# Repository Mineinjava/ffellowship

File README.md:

# ffellowship
Frequency Fellowship: Examining Radio Wave Propagation from a High Altitude Balloon
---

This is a project for Hack Club's [Apex](https://apex.hackclub.com),
made by:
- [Marcus Kauffman](https://kauffman.tools) KN6UYL (@mineinjava)
- Hudson Hilal (@hhilal123)
- Joshua Truman (@jstruman4929)

We initially had two project ideas for Apex: this and dropping what was
effectively a lawn dart from 100,000 feet. After the lawn dart project
was rejected, we submitted this project.

Many high altitude balloons (HABs) have been launched, almost all of
which have some sort of tracker that transmits the balloon's location.
These transmissions are received by stations on the ground and then
uploaded to the internet, from which we can view the locations of
receiving stations for analysis. Our goal for this project is to study
the differences between different tracker design techniques,
specifically:

- Does radio band selection influence likelihood of reception?
    - Receiving stations on the 2m band are much more common than those
      on the 20m band, but 20m transmissions theoretically travel
      farther.
- There are three common methods of modulating signals:
    - Connecting to a dedicated radio for transmission
    - Using a MS5351M or similar clock generator IC
    - Using [fancy PLL](https://github.com/kaduhi/pico-fractional-pll)
      to "bit-bang" the radio waveform

    **Question: do these three modulation methods have a significant
    difference in quality and therefore propagation?**
- How do different antenna designs affect propagation.

Due to customs issues, we were only able to test the PLL tracker 
with three antenna wavelengths. Two of the frequencies had issues 
(unresolved ATM), so we instead analyzed the effect of height on 
radio wave propagation.

As suggested above, this project can easily be divided into three
"sub-projects":

## 1. Use of the MS5351M Clock Generator IC.

This subproject revolves around the MS5351M clock generator. It features
a custom PCB. Note that this tracker will transmit on both the 20m and
2m bands because the MS5351M has multiple clock generators.

This tracker has quite a few features, many of which are to support
ultra-low power operation, as is common with this style of tracker:

- GPS
- Temperature/pressure sensor
- Shunt
- 3v3 buck-boost converter
- power supervisor to restart the pico
- Sensors can be powered off to conserve power.

This PCB is designed around the Raspberry Pi Pico due to its rigorous
testing and ease of integration. It also features mainly 1206 components
to aid in manual reflow soldering of the PCB.

See the dPicoTracker/ directory for more info.

## 2. Use of PLL:

This subproject uses the Raspberry Pi Pico to generate RF signals,
*without the use of a dedicated radio/chip*. It is by far the simplest
design and features a power supervisor, optional low-pass filter, 
battery measurement circuitry, as well as a GPS which is essential 
for correcting oscillator drift.

## 3. Use of a Dedicated HT Radio.

This subproject uses a Raspberry Pi Zero W and a custom PCB to connect
to a HT, which will be stripped down to save weight. 

The PCB consists of a voltage regulator to power the Pi and a 555 timer
circuit to ensure that transmissions are limited in time (in case
of a software crash).

## Integration:

*coming soon*

## Project Status:

*coming soon*

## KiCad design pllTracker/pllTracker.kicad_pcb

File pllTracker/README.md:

# Tracker using PLL

This tracker uses fractional PLL to generate RF on the 20m band.

## BOM:

| Id  | Designator     | Footprint                         | Quantity | Designation         | Supplier and ref |
|-----|----------------|-----------------------------------|----------|---------------------|------------------|
| 1   | C15            | C_1206_3216Metric                 | 1        | 300pF               |   C5449026       |
| 2   | C14,C16        | C_1206_3216Metric                 | 2        | 180pF               |   C3832761       |
| 3   | R6             | C_1206_3216Metric                 | 1        | 100kΩ               |   C137393        |
| 4   | U7             | SOT-23_ONS                        | 1        | MAX809STRG          |   C9965          |
| 6   | R1             | C_1206_3216Metric                 | 1        | 10kΩ                |   C132649        |
| 7   | L5,L4          | L_1206_3216Metric                 | 2        | 560nH               |   C13585         |
| 10  | IC1            | ATGM336H5N31                      | 1        | ATGM336H-5N31       |   C2940946       |
| 11  | C8             | C_1206_3216Metric                 | 2        | 100nF               |   C137393        |
| 13  | Q1, Q2         | Q_SOT-23                          | 1        | AO3401A             |   C15127         |
| 13  | C7             | C_1206_3216Metric                 | 1        | 1nF                 |   C23631         |
| 14  | R5             | D_1206_3216Metric                 | 1        | 200kΩ               |   C114937        |

Additionally:
- 1 GPS antenna
- 1 20m antenna
- 1 Raspberry Pi Pico

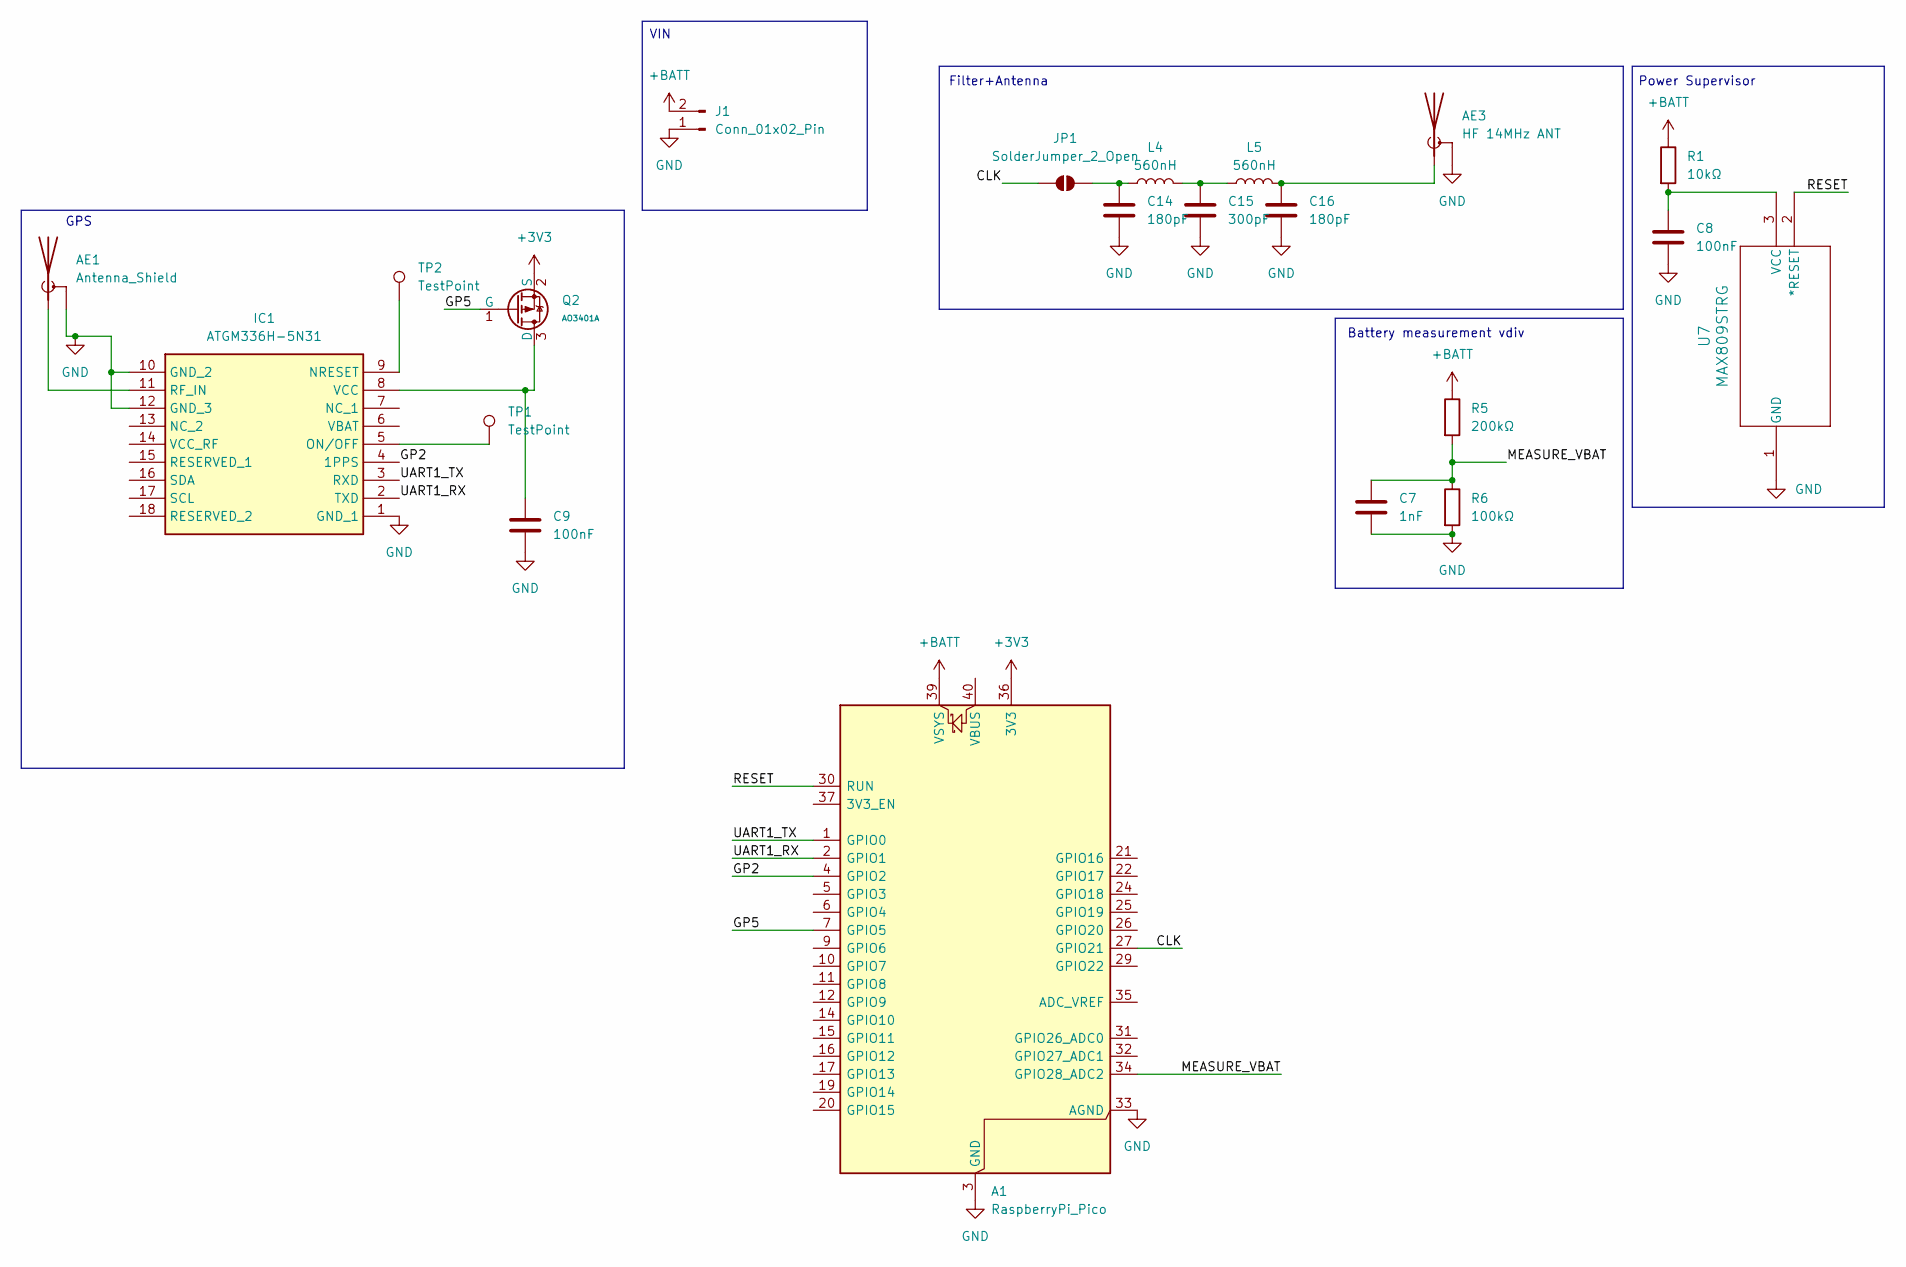
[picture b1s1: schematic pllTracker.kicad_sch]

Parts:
A1: RaspberryPi_Pico; RaspberryPi_Pico_Common_Unspecified
AE1: Antenna_Shield; PinSocket_1x02_P2.54mm_Vertical
AE3: HF 14MHz ANT; PinHeader_1x02_P2.54mm_Vertical
C7: 1nF; C_1206_3216Metric
C8, C9: 100nF; C_1206_3216Metric
C14, C16: 180pF; C_1206_3216Metric
C15: 300pF; C_1206_3216Metric
IC1: ATGM336H-5N31; ATGM336H5N31; Manufacturer_Part_Number ATGM336H-5N31
J1: Conn_01x02_Pin; PinSocket_1x02_P2.54mm_Vertical
JP1: SolderJumper_2_Open; SolderJumper-2_P1.3mm_Open_Pad1.0x1.5mm
L4, L5: 560nH; L_1206_3216Metric
Q2: AO3401A; Q_SOT-23; Part AO3401A; LCSC C15127
R1: 10kΩ; C_1206_3216Metric
R5: 200kΩ; D_1206_3216Metric
R6: 100kΩ; C_1206_3216Metric
TP1, TP2: TestPoint; TestPoint_Pad_D1.5mm
U7: MAX809STRG; SOT-23_ONS

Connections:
+3V3: A1.36 (3V3), Q2.2 (S)
+BATT: A1.39 (VSYS), J1.2, R1.1, R5.1
/CLK: A1.27 (GPIO21), JP1.1 (A)
/GP2: A1.4 (GPIO2), IC1.4 (1PPS)
/GP5: A1.7 (GPIO5), Q2.1 (G)
/MEASURE_VBAT: A1.34 (GPIO28_ADC2), C7.2, R5.2, R6.1
/RESET: A1.30 (RUN), U7.2 (*RESET)
/UART1_RX: A1.2 (GPIO1), IC1.2 (TXD)
/UART1_TX: A1.1 (GPIO0), IC1.3 (RXD)
GND: A1.3 (GND), A1.8 (GND), A1.13 (GND), A1.18 (GND), A1.23 (GND), A1.28 (GND), A1.33 (AGND), A1.38 (GND), AE1.2 (Shield), AE3.2 (Shield), C7.1, C8.2, C9.2, C14.2, C15.2, C16.2, IC1.1 (GND_1), IC1.10 (GND_2), IC1.12 (GND_3), J1.1, R6.2, U7.1 (GND)
unnamed: AE1.1 (A), IC1.11 (RF_IN)
unnamed: AE3.1 (A), C16.1, L5.2
unnamed: C15.1, L4.2, L5.1
unnamed 13: IC1.9 (NRESET), TP2.1; also elsewhere on the board
unnamed 14: IC1.5 (ON/OFF), TP1.1; also elsewhere on the board
unnamed: C9.1, IC1.8 (VCC), Q2.3 (D)
unnamed: C14.1, JP1.2 (B), L4.1
unnamed: C8.1, R1.2, U7.3 (VCC)

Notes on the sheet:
Power Supervisor
VIN
GPS
Filter+Antenna
Battery measurement vdiv

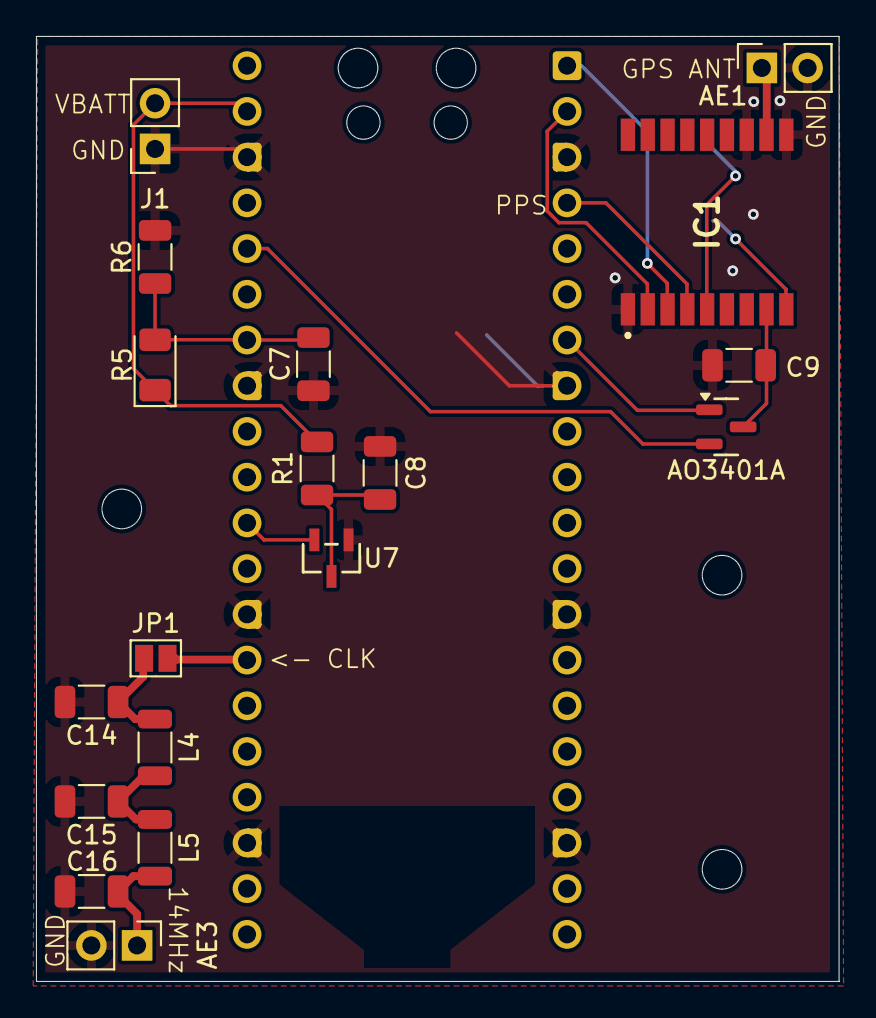
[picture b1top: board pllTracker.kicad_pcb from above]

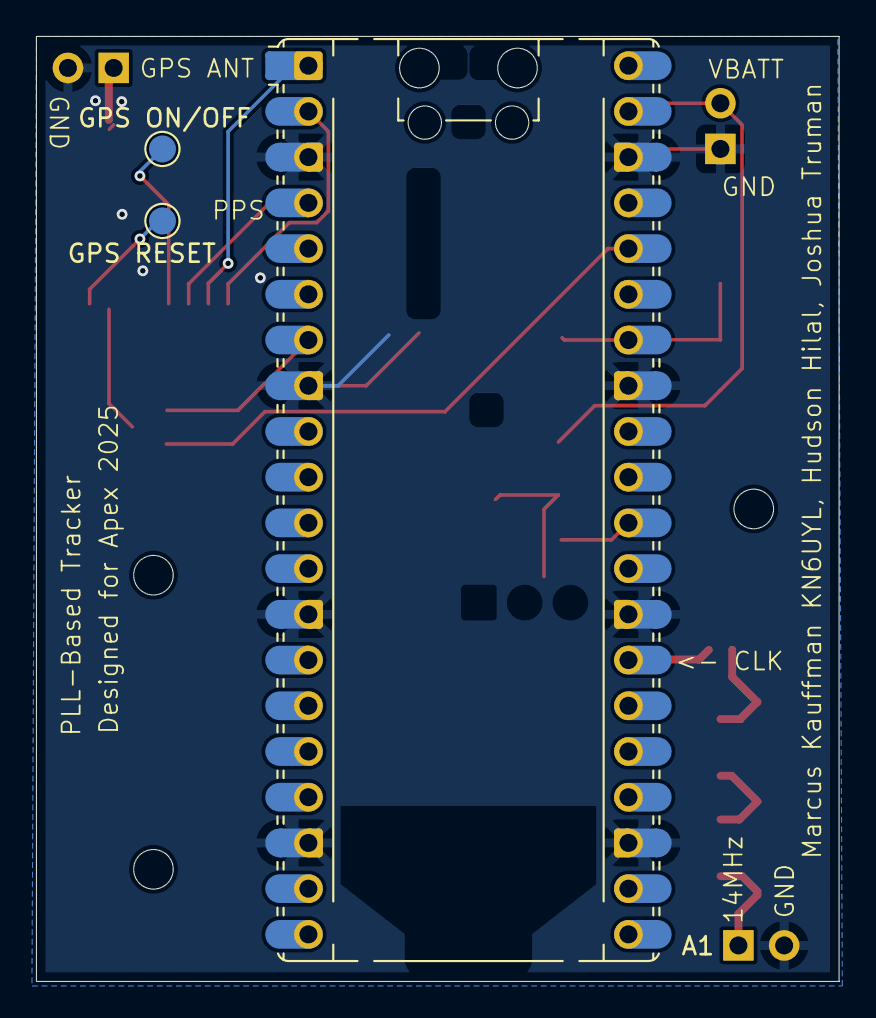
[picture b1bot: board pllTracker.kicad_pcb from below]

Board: 2 copper layers, 44.6 x 52.5 mm, 21 parts (3 on the bottom side), 18 nets.

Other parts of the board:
GPS ON/OFF: TestPoint; TestPoint_Pad_D1.5mm
GPS RESET: TestPoint; TestPoint_Pad_D1.5mm

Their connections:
unnamed 13: GPS RESET.1; also elsewhere on the board
unnamed 14: GPS ON/OFF.1; also elsewhere on the board

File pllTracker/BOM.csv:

Comment,Designator,Footprint,LCSC Part #,Quantity
300pF,C15,C_1206_3216Metric,C5449026,1
180pF,C14C16,C_1206_3216Metric,C3832761,2
100kΩ,R6,C_1206_3216Metric,C137393,1
MAX809STRG,U7,SOT-23_ONS,C9965,1
10kΩ,R1,C_1206_3216Metric,C132649,1
560nH,L5L4,L_1206_3216Metric,C13585,2
ATGM336H-5N31,IC1,ATGM336H5N31,C2940946,1
100nF,C8,C_1206_3216Metric,C137393,2
AO3401A,Q1Q2,Q_SOT-23,C15127,1
1nF,C7,C_1206_3216Metric,C23631,1
200kΩ,R5,D_1206_3216Metric,C114937,1

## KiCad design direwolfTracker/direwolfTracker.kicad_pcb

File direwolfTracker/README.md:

# Direwolf-powered Tracker

This tracker uses direwolf to communicate with an external radio like a
HT.

## BOM:

| Id  | Designator           | Footprint                           | Quantity | Designation       | Supplier and ref |
|-----|----------------------|-------------------------------------|----------|-------------------|------------------|
| 1   | C2, C1, C3           | C_1206_3216Metric                   | 3        | 10µF              |    C13585        |
| 3   | Q1                   | Q_SOT-23                            | 1        | MMBT2222A         |    C82460        |
| 4   | C20, C19, C21        | C_1206_3216Metric                   | 3        | 100nF             |    C82460        |
| 7   | U1                   | Texas_R-PDSO-G6                     | 1        | TPS61222DCK       |    C116461       |
| 9   | R1                   | R_1206_3216Metric                   | 1        | 10kΩ              |    C132649       |
| 10  | R3                   | R_1206_3216Metric                   | 1        | 2.7kΩ             |    C2930416      |
| 12  | IC1                  | ATGM336H5N31                        | 1        | ATGM336H-5N31     |    C2940946      |
| 13  | R2                   | R_1206_3216Metric                   | 1        | 100kΩ             |    C2930416      |
| 14  | U2                   | DIP-8_W7.62mm                       | 1        | ICM7555xP         |    C22461592     |
| 15  | R4                   | R_1206_3216Metric                   | 1        | 1MΩ               |    C108083       |
| 16  | L1                   | L_1206_3216Metric                   | 1        | 4.7µH             |    C13585        |

Additionally:
- 1 Raspberry Pi Zero
- 1 GPS Antenna
- 1 micro usb sound card
- 1 TRRS 3.5mm cable
- 1 TRS 3.5mm cable
- 1 TRS 2.5mm cable
- 1 external radio

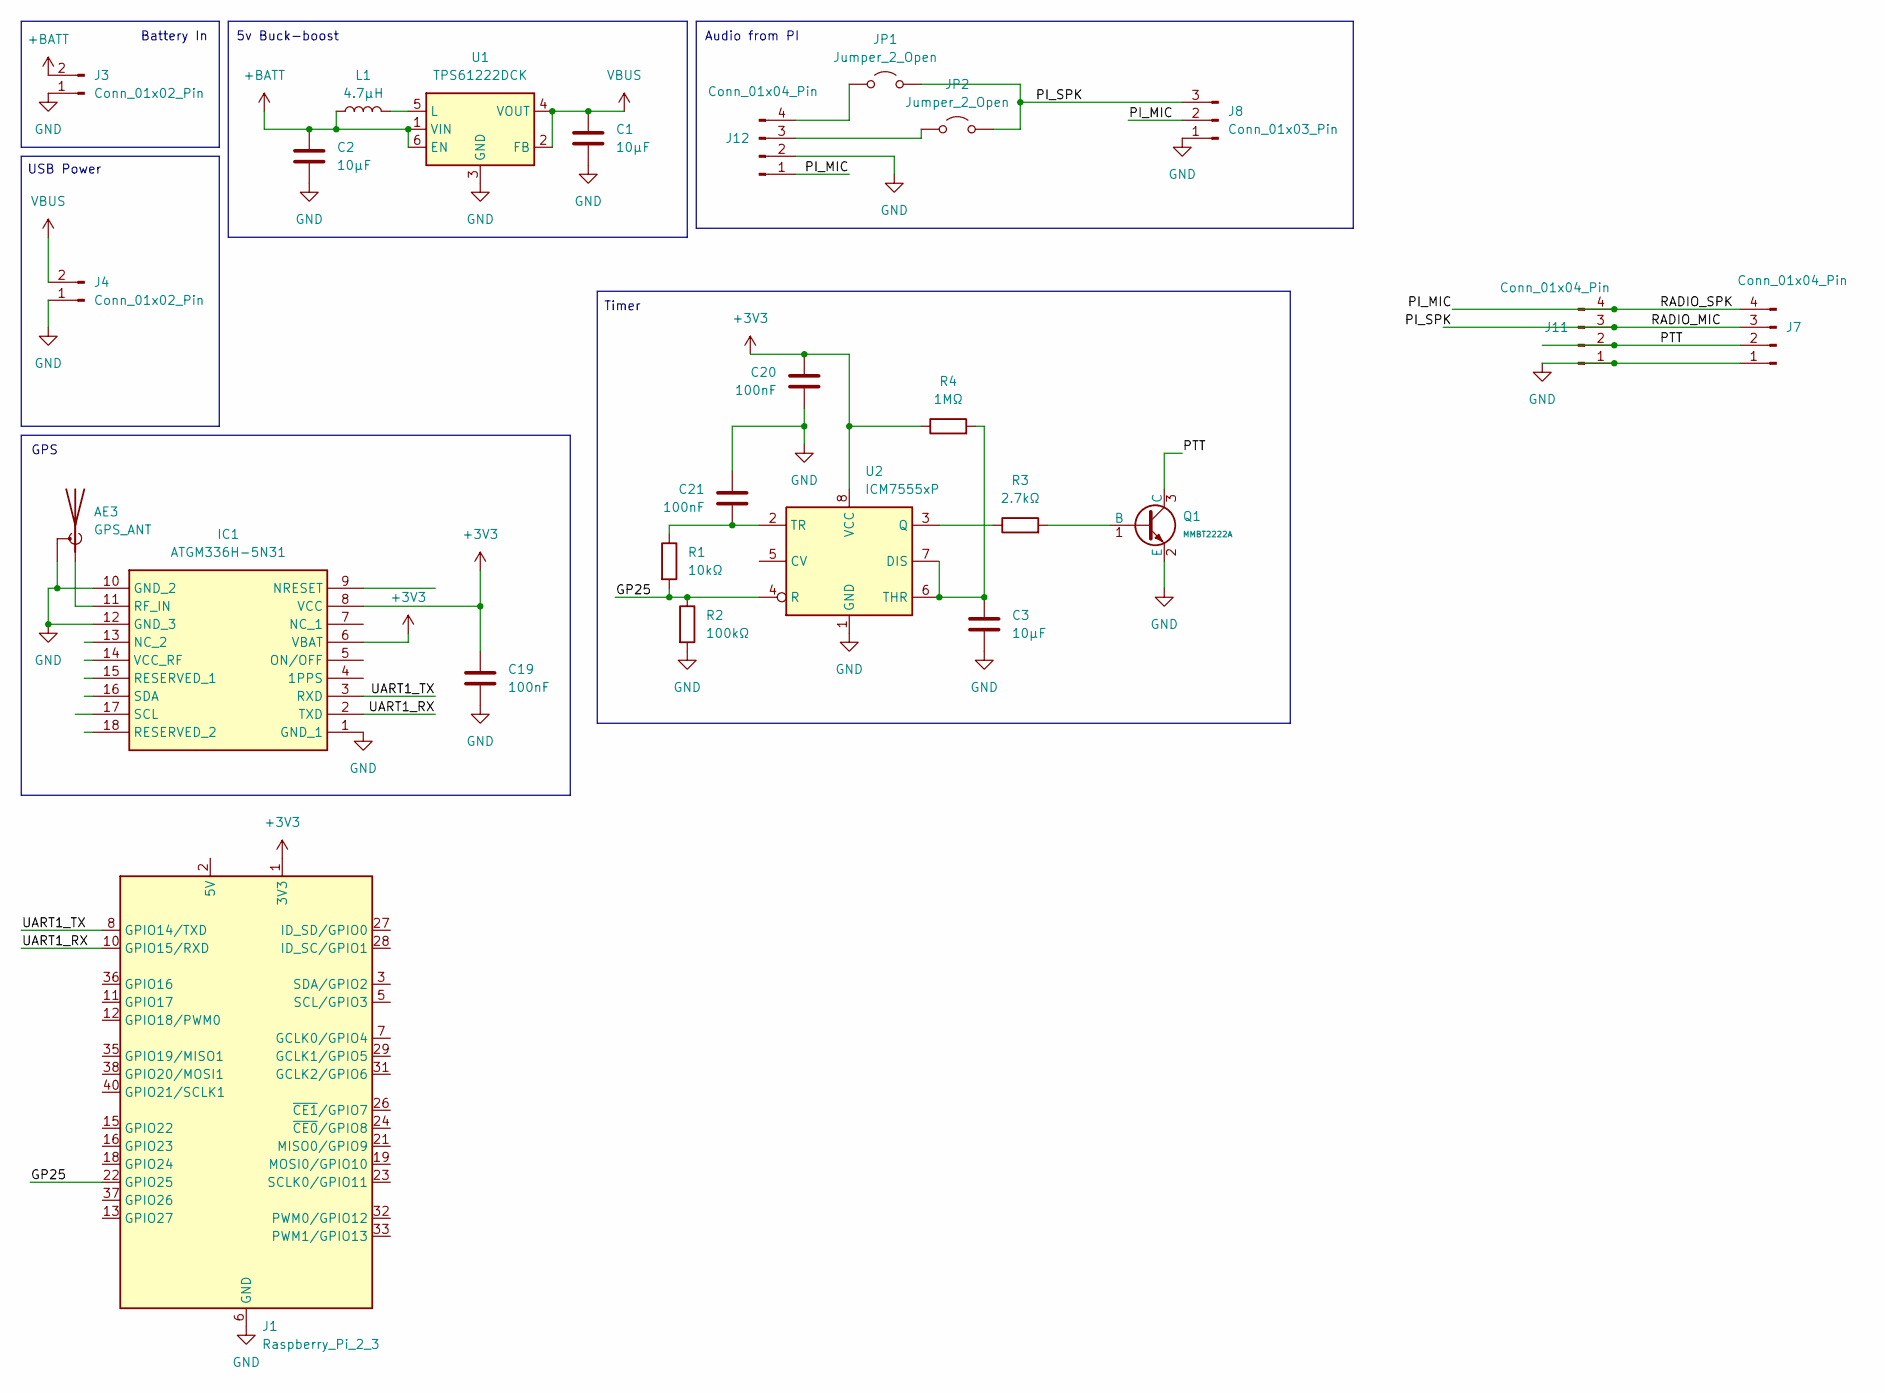
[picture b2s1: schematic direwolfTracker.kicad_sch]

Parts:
AE3: GPS_ANT; PinHeader_1x02_P2.54mm_Vertical
C1, C2, C3: 10µF; C_1206_3216Metric
C19, C20, C21: 100nF; C_1206_3216Metric
IC1: ATGM336H-5N31; ATGM336H5N31; Manufacturer_Part_Number ATGM336H-5N31
J1: Raspberry_Pi_2_3; PinHeader_2x20_P2.54mm_Vertical
J3, J4: Conn_01x02_Pin; PinSocket_1x02_P2.54mm_Vertical
J7, J11, J12: Conn_01x04_Pin; PinHeader_1x04_P2.54mm_Vertical
J8: Conn_01x03_Pin; PinSocket_1x03_P2.54mm_Vertical
JP1, JP2: Jumper_2_Open; TestPoint_2Pads_Pitch2.54mm_Drill0.8mm
L1: 4.7µH; L_1206_3216Metric
Q1: MMBT2222A; Q_SOT-23; Part MMBT2222A; LCSC C7420351
R1: 10kΩ; R_1206_3216Metric
R2: 100kΩ; R_1206_3216Metric
R3: 2.7kΩ; R_1206_3216Metric
R4: 1MΩ; R_1206_3216Metric
U1: TPS61222DCK; Texas_R-PDSO-G6
U2: ICM7555xP; DIP-8_W7.62mm

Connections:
+3V3: C19.1, C20.1, IC1.6 (VBAT), IC1.8 (VCC), J1.1 (3V3), J1.17 (3V3), R4.1, U2.8 (VCC)
+BATT: C2.1, J3.2, L1.1, U1.1 (VIN), U1.6 (EN)
/GP25: J1.22 (GPIO25), R1.2, R2.1, U2.4 (R)
/PI_MIC: J7.4, J8.2, J11.4, J12.1
/PI_SPK: J7.3, J8.3, J11.3, JP1.2 (B), JP2.2 (B)
/PTT: J7.2, J11.2, Q1.3 (C)
/UART1_RX: IC1.2 (TXD), J1.10 (GPIO15/RXD)
/UART1_TX: IC1.3 (RXD), J1.8 (GPIO14/TXD)
GND: AE3.2 (Shield), C1.2, C2.2, C3.2, C19.2, C20.2, C21.1, IC1.1 (GND_1), IC1.10 (GND_2), IC1.12 (GND_3), J1.6 (GND), J1.9 (GND), J1.14 (GND), J1.20 (GND), J1.25 (GND), J1.30 (GND), J1.34 (GND), J1.39 (GND), J3.1, J4.1, J7.1, J8.1, J11.1, J12.2, Q1.2 (E), R2.2, U1.3 (GND), U2.1 (GND)
unnamed: AE3.1 (A), IC1.11 (RF_IN)
unnamed: J1.2 (5V), J1.4 (5V)
unnamed: J12.3, JP2.1 (A)
unnamed: J12.4, JP1.1 (A)
unnamed: Q1.1 (B), R3.2
unnamed: L1.2, U1.5 (L)
unnamed: C3.1, R4.2, U2.6 (THR), U2.7 (DIS)
unnamed: R3.1, U2.3 (Q)
unnamed: C21.2, R1.1, U2.2 (TR)
VBUS: C1.1, J4.2, U1.2 (FB), U1.4 (VOUT)

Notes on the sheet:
Battery In
GPS
5v Buck-boost
Timer
Audio from PI
USB Power

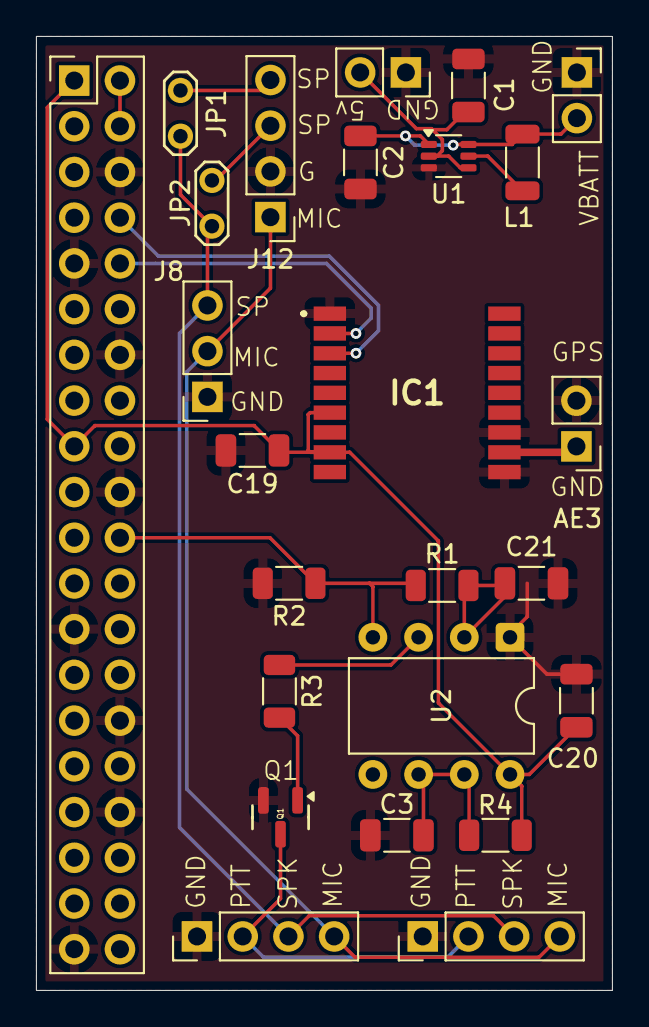
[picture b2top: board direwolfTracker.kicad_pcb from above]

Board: 2 copper layers, 32.0 x 53.0 mm, 25 parts (0 on the bottom side), 19 nets.

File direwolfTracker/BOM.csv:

Comment,Designator,Footprint,LCSC Part #,Quantity
10µF,C2C1C3,C_1206_3216Metric,C13585,3
MMBT2222A,Q1,Q_SOT-23,C82460,1
100nF,C20C19C21,C_1206_3216Metric,C82460,3
TPS61222DCK,U1,Texas_R-PDSO-G6,C116461,1
10kΩ,R1,R_1206_3216Metric,C132649,1
2.7kΩ,R3,R_1206_3216Metric,C2930416,1
ATGM336H-5N31,IC1,ATGM336H5N31,C2940946,1
100kΩ,R2,R_1206_3216Metric,C2930416,1
ICM7555xP,U2,DIP-8_W7.62mm,C22461592,1
1MΩ,R4,R_1206_3216Metric,C108083,1
4.7µH,L1,L_1206_3216Metric,C13585,1

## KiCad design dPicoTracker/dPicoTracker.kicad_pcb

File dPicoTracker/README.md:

# Tracker With MS5351M IC

This tracker uses the MS5351M IC to generate RF.

## BOM:

| Id  | Designator                        | Footprint                                         | Quantity | Designation         | Supplier and ref | 
|-----|----------------------------------|---------------------------------------------------|----------|----------------------|------------------|
| 1   | L1                               | L_1206_3216Metric                                 | 1        | 4.7µH               |      C13585       |
| 2   | C14, C16                         | C_1206_3216Metric                                 | 2        | 18pF                |      C565686      |
| 3   | L4, L5                           | L_1206_3216Metric                                 | 2        | 56nH                |      C13585       |
| 4   | U7                               | SOT-23_ONS                                        | 1        | MAX809STRG          |      C9965        |
| 6   | U8                               | Bosch_LGA-8_2x2.5mm_P0.65mm                       | 1        | BMP280              |      C83291       |
| 7   | Y1                               | MSOP-10_3x3mm_P0.5mm                              | 1        | Si5351A-B-GT        |      C1509083     |
| 8   | C9, C19, C1, C8, C17, C18, C10   | C_1206_3216Metric                                 | 7        | 100nF               |      C24497       |
| 10  | Y2                               | Crystal_SMD_2520-4Pin_2.5x2.0mm                   | 1        | C132296             |      C132296      |
| 11  | L3, L2                           | L_1206_3216Metric                                 | 2        | 560nH               |      C13585       |
| 12  | R6                               | C_1206_3216Metric                                 | 1        | 100kΩ               |      C137393      |
| 13  | Q1, Q2                           | Q_SOT-23                                          | 2        | AO3401A             |      C15127       |
| 15  | R8, R14, R15, R11, R9, R12       | R_1206_3216Metric                                 | 6        | 10kΩ                |      C132649      |
| 16  | C15                              | C_1206_3216Metric                                 | 1        | 30pF                |      C1905        |
| 17  | C12                              | C_1206_3216Metric                                 | 1        | 300pF               |      C5449026     |
| 18  | C5                               | C_1206_3216Metric                                 | 1        | 10µF                |      C13585       |
| 19  | C11, C13                         | C_1206_3216Metric                                 | 2        | 180pF               |      C3832761     |
| 20  | IC1                              | ATGM336H5N31                                      | 1        | ATGM336H-5N31       |      C2940946     |
| 21  | U3, U4                           | SOT-23-3_L2.9-W1.6-P1.90-LS2.8-BR                 | 2        | CJ431               |      C3113        |
| 22  | R7                               | C_1206_3216Metric                                 | 1        | 10kΩ                |      C132649      |
| 23  | U5                               | Texas_R-PDSO-G6                                   | 1        | TPS61221DCK         |      C2865756     |
| 24  | C7                               | C_1206_3216Metric                                 | 1        | 1nF                 |      C23631       |
| 25  | R5                               | D_1206_3216Metric                                 | 1        | 200kΩ               |      C114937      |

Additionally:
- 1x GPS antenna
- 1x 2m antenna
- 1x 20m antenna
- 1x Raspberry Pi Pico

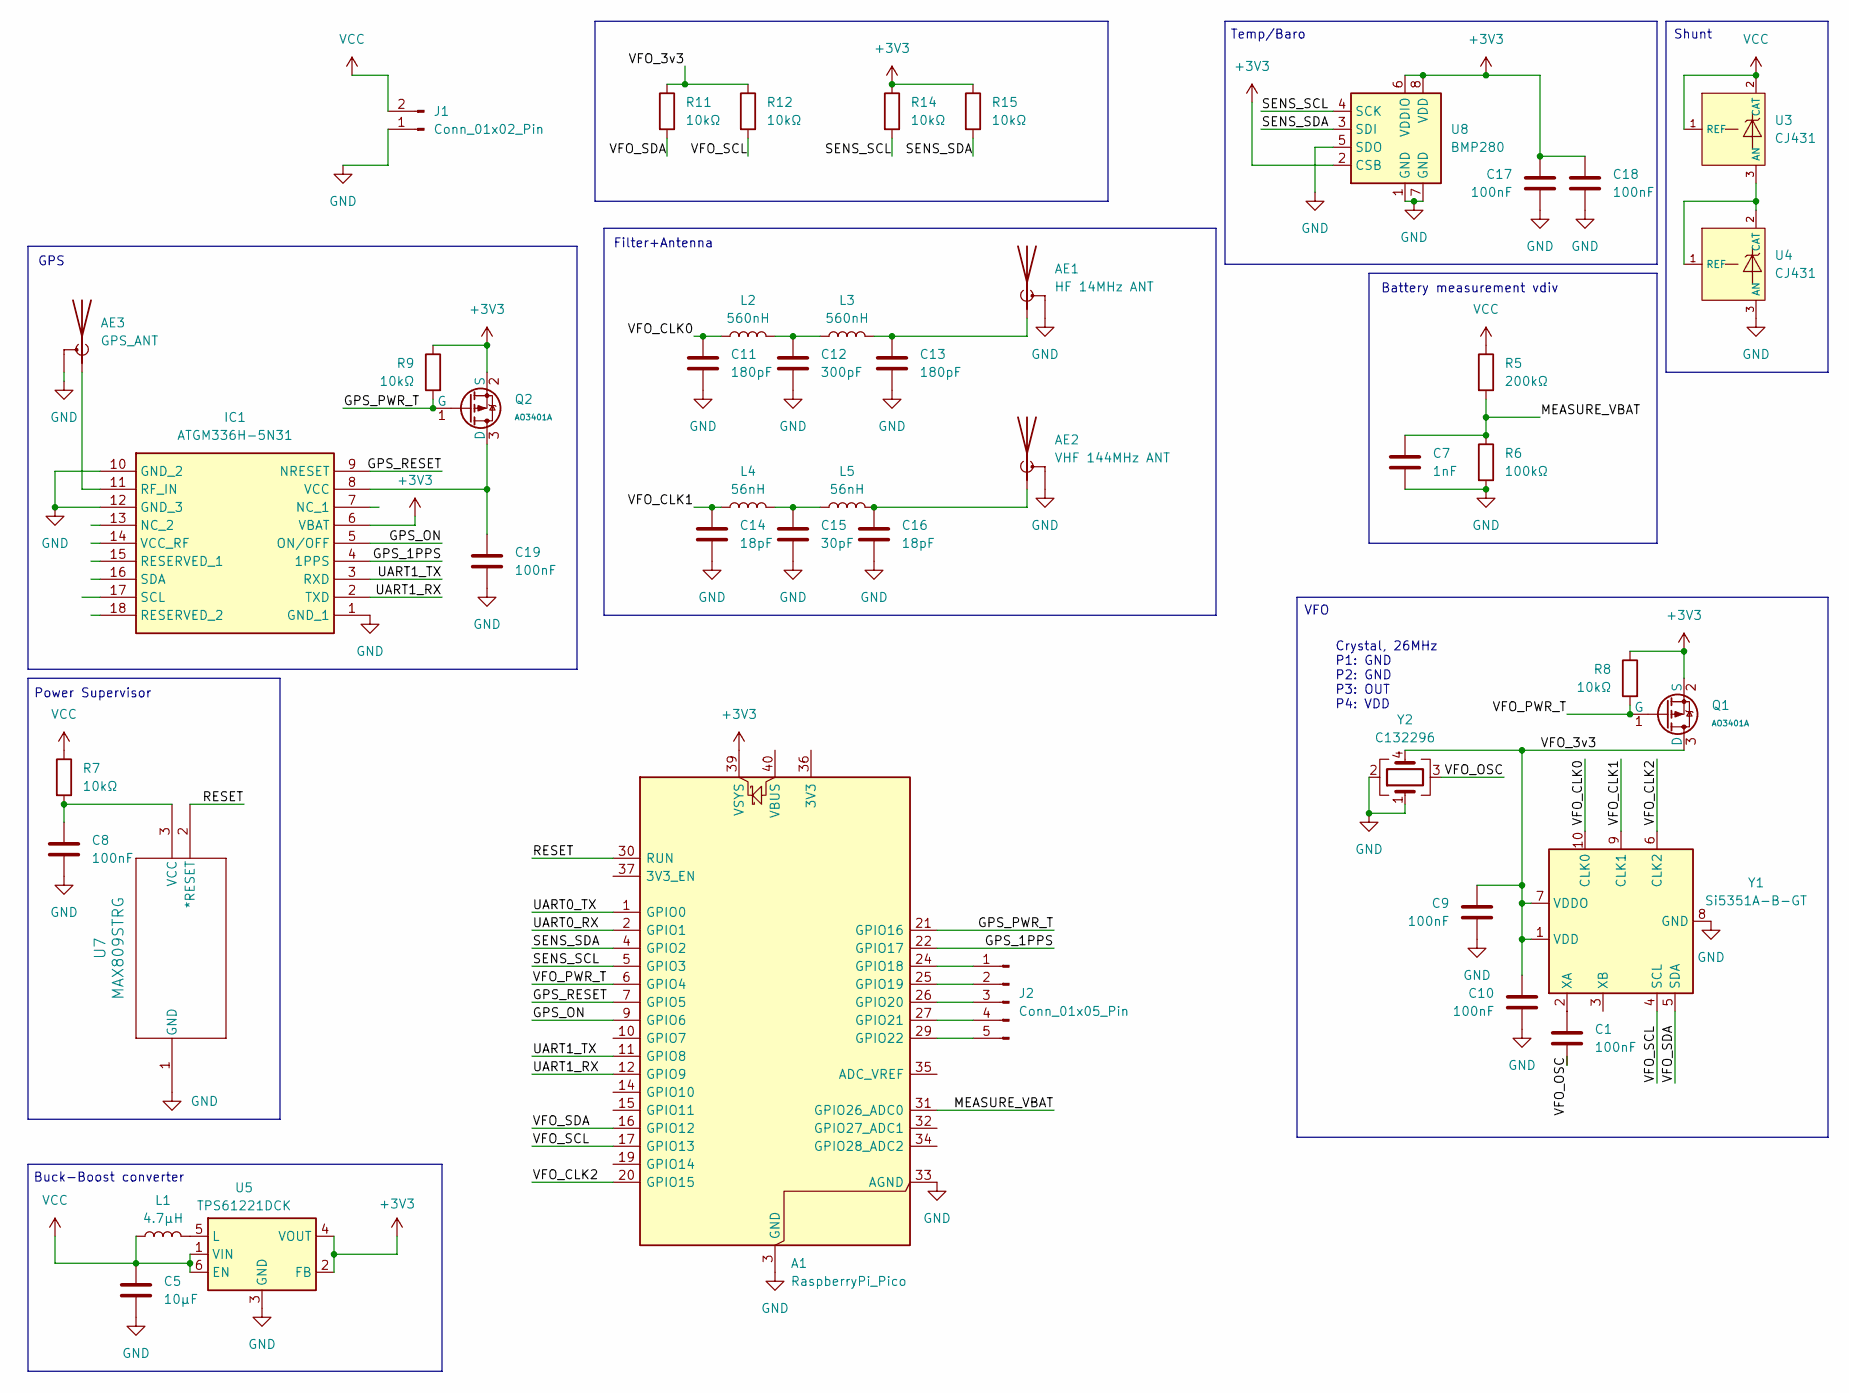
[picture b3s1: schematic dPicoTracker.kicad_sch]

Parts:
A1: RaspberryPi_Pico; RaspberryPi_Pico_Common_Unspecified
AE1: HF 14MHz ANT; PinHeader_1x02_P2.54mm_Vertical
AE2: VHF 144MHz ANT; PinHeader_1x02_P2.54mm_Vertical
AE3: GPS_ANT; PinHeader_1x02_P2.54mm_Vertical
C1, C8, C9, C10, C17, C18, C19: 100nF; C_1206_3216Metric
C5: 10µF; C_1206_3216Metric
C7: 1nF; C_1206_3216Metric
C11, C13: 180pF; C_1206_3216Metric
C12: 300pF; C_1206_3216Metric
C14, C16: 18pF; C_1206_3216Metric
C15: 30pF; C_1206_3216Metric
IC1: ATGM336H-5N31; ATGM336H5N31; Manufacturer_Part_Number ATGM336H-5N31
J1: Conn_01x02_Pin; PinSocket_1x02_P2.00mm_Vertical
J2: Conn_01x05_Pin; PinSocket_1x05_P2.54mm_Vertical
L1: 4.7µH; L_1206_3216Metric
L2, L3: 560nH; L_1206_3216Metric
L4, L5: 56nH; L_1206_3216Metric
Q1, Q2: AO3401A; Q_SOT-23; Part AO3401A; LCSC C15127
R5: 200kΩ; D_1206_3216Metric
R6: 100kΩ; C_1206_3216Metric
R7: 10kΩ; C_1206_3216Metric
R8, R9, R11, R12, R14, R15: 10kΩ; R_1206_3216Metric
U3, U4: CJ431; SOT-23-3_L2.9-W1.6-P1.90-LS2.8-BR; Output Voltage 2.5V~36V; Tolerance ±0.5%; Part CJ431; LCSC C3113
U5: TPS61221DCK; Texas_R-PDSO-G6
U7: MAX809STRG; SOT-23_ONS
U8: BMP280; Bosch_LGA-8_2x2.5mm_P0.65mm_ClockwisePinNumbering
Y1: Si5351A-B-GT; MSOP-10_3x3mm_P0.5mm
Y2: C132296; Crystal_SMD_2520-4Pin_2.5x2.0mm

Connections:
+3V3: A1.39 (VSYS), C17.1, C18.1, IC1.6 (VBAT), Q1.2 (S), Q2.2 (S), R8.1, R9.1, R14.1, R15.1, U5.2 (FB), U5.4 (VOUT), U8.2 (CSB), U8.6 (VDDIO), U8.8 (VDD)
/GPS_1PPS: A1.22 (GPIO17), IC1.4 (1PPS)
/GPS_ON: A1.9 (GPIO6), IC1.5 (ON/OFF)
/GPS_PWR_T: A1.21 (GPIO16), Q2.1 (G), R9.2
/GPS_RESET: A1.7 (GPIO5), IC1.9 (NRESET)
/MEASURE_VBAT: A1.31 (GPIO26_ADC0), C7.2, R5.2, R6.1
/RESET: A1.30 (RUN), U7.2 (*RESET)
/SENS_SCL: A1.5 (GPIO3), R14.2, U8.4 (SCK)
/SENS_SDA: A1.4 (GPIO2), R15.2, U8.3 (SDI)
/UART0_RX: A1.2 (GPIO1)
/UART0_TX: A1.1 (GPIO0)
/UART1_RX: A1.12 (GPIO9), IC1.2 (TXD)
/UART1_TX: A1.11 (GPIO8), IC1.3 (RXD)
/VFO_3v3: C9.1, C10.1, Q1.3 (D), R11.1, R12.1, Y1.1 (VDD), Y1.7 (VDDO), Y2.4
/VFO_CLK0: C11.1, L2.1, Y1.10 (CLK0)
/VFO_CLK1: C14.1, L4.1, Y1.9 (CLK1)
/VFO_CLK2: A1.20 (GPIO15), Y1.6 (CLK2)
/VFO_OSC: C1.1, Y2.3
/VFO_PWR_T: A1.6 (GPIO4), Q1.1 (G), R8.2
/VFO_SCL: A1.17 (GPIO13), R12.2, Y1.4 (SCL)
/VFO_SDA: A1.16 (GPIO12), R11.2, Y1.5 (SDA)
GND: A1.3 (GND), A1.8 (GND), A1.13 (GND), A1.18 (GND), A1.23 (GND), A1.28 (GND), A1.33 (AGND), A1.38 (GND), AE1.2 (Shield), AE2.2 (Shield), AE3.2 (Shield), C5.2, C7.1, C8.2, C9.2, C10.2, C11.2, C12.2, C13.2, C14.2, C15.2, C16.2, C17.2, C18.2, C19.2, IC1.1 (GND_1), IC1.10 (GND_2), IC1.12 (GND_3), J1.1, R6.2, U4.3 (AN), U5.3 (GND), U7.1 (GND), U8.1 (GND), U8.5 (SDO), U8.7 (GND), Y1.8 (GND), Y2.1, Y2.2
unnamed: A1.24 (GPIO18), J2.1
unnamed: A1.25 (GPIO19), J2.2
unnamed: A1.26 (GPIO20), J2.3
unnamed: A1.27 (GPIO21), J2.4
unnamed: A1.29 (GPIO22), J2.5
unnamed: AE1.1 (A), C13.1, L3.2
unnamed: AE2.1 (A), C16.1, L5.2
unnamed: AE3.1 (A), IC1.11 (RF_IN)
unnamed: C12.1, L2.2, L3.1
unnamed: C15.1, L4.2, L5.1
unnamed: C19.1, IC1.8 (VCC), Q2.3 (D)
unnamed: U3.3 (AN), U4.1 (REF), U4.2 (CAT)
unnamed: L1.2, U5.5 (L)
unnamed: C8.1, R7.2, U7.3 (VCC)
unnamed: C1.2, Y1.2 (XA)
VCC: C5.1, J1.2, L1.1, R5.1, R7.1, U3.1 (REF), U3.2 (CAT), U5.1 (VIN), U5.6 (EN)

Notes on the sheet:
Filter+Antenna
Buck-Boost converter
Battery measurement vdiv
GPS
Shunt
Crystal, 26MHz P1: GND P2: GND P3: OUT P4: VDD
Power Supervisor
VFO
Temp/Baro

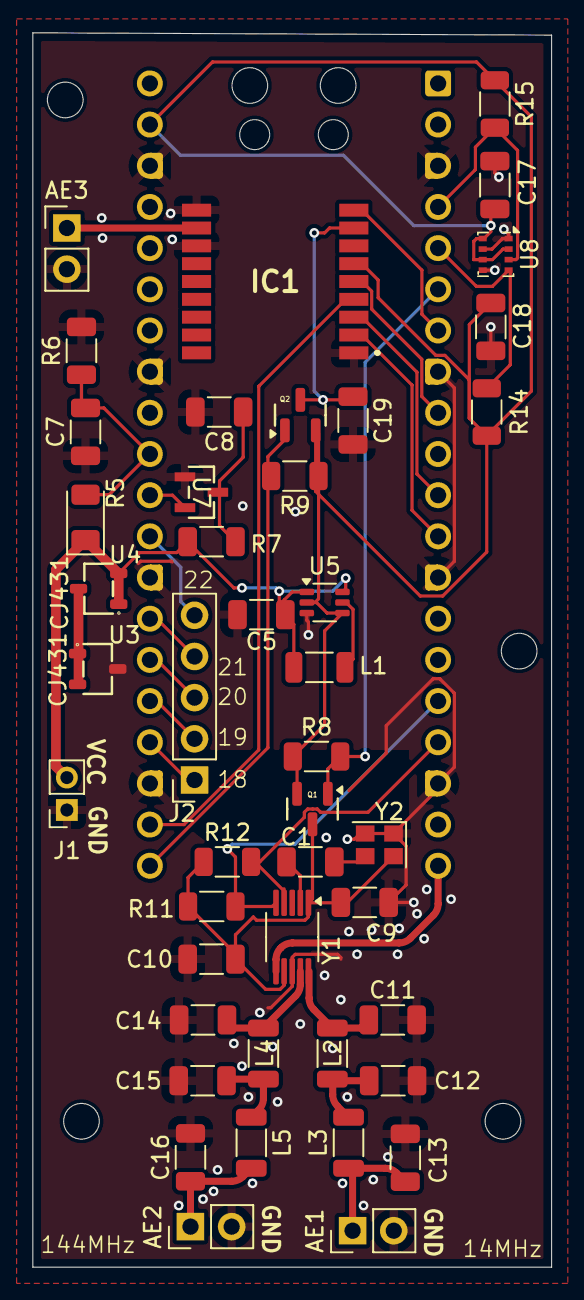
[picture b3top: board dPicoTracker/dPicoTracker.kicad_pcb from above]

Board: 2 copper layers, 32.0 x 76.1 mm, 45 parts (1 on the bottom side), 36 nets.

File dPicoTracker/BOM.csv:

Comment,Designator,Footprint,LCSC Part #,Quantity
4.7µH,L1,L_1206_3216Metric,C13585,1
18pF,C14C16,C_1206_3216Metric,C565686,2
56nH,L4L5,L_1206_3216Metric,C13585,2
MAX809STRG,U7,SOT-23_ONS,C9965,1
BMP280,U8,Bosch_LGA-8_2x2.5mm_P0.65mm,C83291,1
Si5351A-B-GT,Y1,MSOP-10_3x3mm_P0.5mm,C1509083,1
100nF,C9C19C1C8C17C18C10,C_1206_3216Metric,C24497,7
C132296,Y2,Crystal_SMD_2520-4Pin_2.5x2.0mm,C132296,1
560nH,L3L2,L_1206_3216Metric,C13585,2
100kΩ,R6,C_1206_3216Metric,C137393,1
AO3401A,Q1Q2,Q_SOT-23,C15127,2
10kΩ,R8R14R1R11R9R12,R_1206_3216Metric,C132649,6
30pF,C15,C_1206_3216Metric,C1905,1
300pF,C12,C_1206_3216Metric,C5449026,1
10µF,C5,C_1206_3216Metric,C13585,1
180pF,C11C13,C_1206_3216Metric,C3832761,2
ATGM336H-5N31,IC1,ATGM336H5N31,C2940946,1
CJ431,U3U4,SOT-23-3_L2.9-W1.6-P1.90-LS2.8-BR,C3113,2
10kΩ,R7,C_1206_3216Metric,C132649,1
TPS61221DCK,U5,Texas_R-PDSO-G6,C2865756,1
1nF,C7,C_1206_3216Metric,C23631,1
200kΩ,R5,D_1206_3216Metric,C114937,1

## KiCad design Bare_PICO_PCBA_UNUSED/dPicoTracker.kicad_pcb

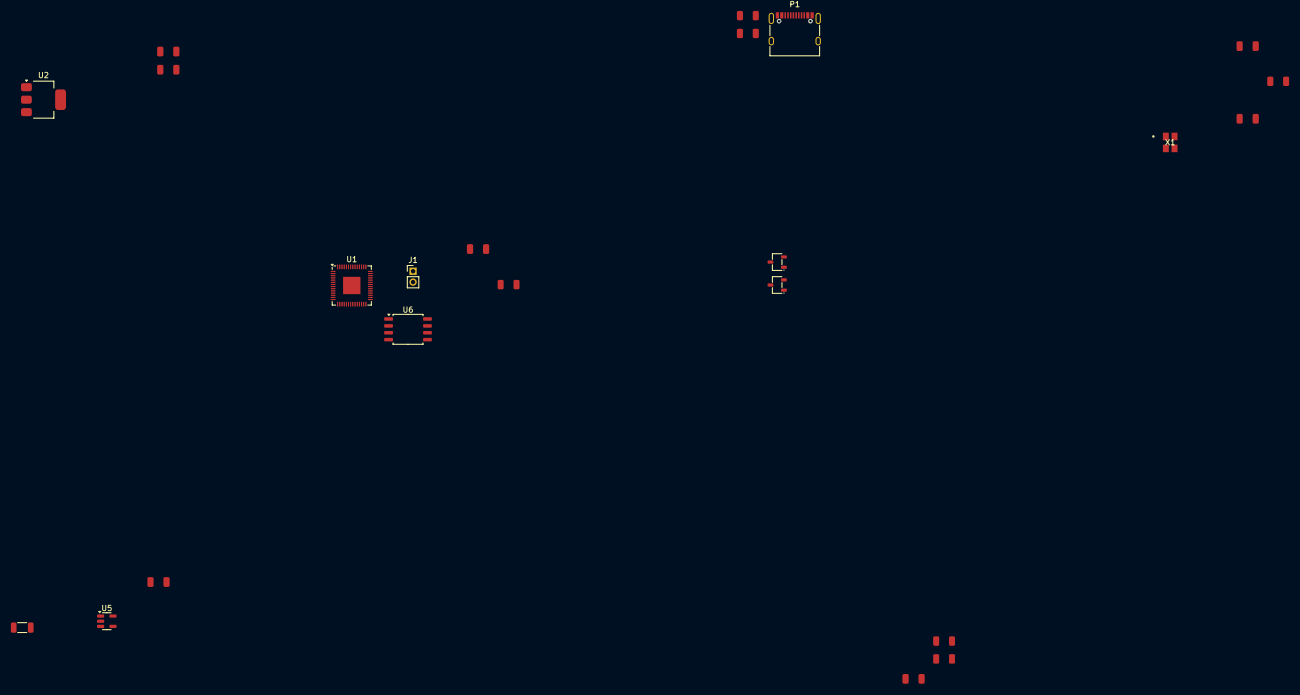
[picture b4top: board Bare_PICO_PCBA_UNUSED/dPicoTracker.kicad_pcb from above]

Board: 2 copper layers, 23 parts (0 on the bottom side), 14 nets, no tracks yet.

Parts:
C1: 100nF; C_1206
C2, C6: 15pF; C_1206
C3, C4, C5: 10µF; C_1206
C7: 1nF; C_1206
J1: Conn_01x02_Pin; PinHeader_1x02_P2.00mm_Vertical
L1: 4.7µH; L_1206
P1: USB_C_Plug_USB2.0; USB_C_Receptacle_XKB_U262-16XN-4BVC11
R1, R2: 5.1kΩ; R_1206
R3, R4: 1kΩ; R_1206
R5: 200kΩ; R_1206
R6: 100kΩ; R_1206
U1: RP2040; QFN-56-1EP_7x7mm_P0.4mm_EP3.2x3.2mm
U2: NCP1117-3.3_SOT223; SOT-223-3_TabPin2
U3, U4: CJ431; SOT-23-3_L2.9-W1.6-P1.90-LS2.8-BR
U5: TPS61221DCK; SOT-23-5
U6: W25Q128JVS; SOIC-8_5.3x5.3mm_P1.27mm
X1: ABM8-272-T3; ABM8-272-T3_ABR

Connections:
+3V3: C1.1, C4.1, U2.2 (VO), U5.2 (FB), U5.4 (VOUT), U6.8 (VCC)
/MEASURE_VBAT: C7.2, R5.2, R6.1
/QSPI_SS: R3.2, U6.1 (~CS)
/XIN: C2.2, X1.1
GND: C1.2, C2.1, C3.2, C4.2, C5.2, C6.2, C7.1, J1.1, P1.A1 (GND), P1.A12 (GND), P1.B1 (GND), P1.B12 (GND), P1.S1 (SHIELD), R1.2, R2.2, R6.2, U2.1 (GND), U4.3 (AN), U5.3 (GND), U6.4 (GND), X1.2, X1.4
unnamed: C6.1, R4.1, X1.3
unnamed: J1.2, R3.1
unnamed: P1.A5 (CC), R1.1, R2.1
unnamed: U1.23 (DVDD), U1.50 (DVDD)
unnamed: U1.1 (IOVDD), U1.10 (IOVDD), U1.22 (IOVDD), U1.33 (IOVDD), U1.42 (IOVDD), U1.49 (IOVDD)
unnamed: U3.3 (AN), U4.1 (REF), U4.2 (CAT)
unnamed: L1.2, U5.5 (L)
VBUS: C3.1, C5.1, L1.1, P1.A4 (VBUS), P1.A9 (VBUS), P1.B4 (VBUS), P1.B9 (VBUS), R5.1, U2.3 (VI), U5.1 (VIN)
VCC: U3.1 (REF), U3.2 (CAT)

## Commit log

2025-05-11 I think halfway there
2025-05-11 add schematic
2025-05-11 Add power supervisor
2025-05-12 add VFO
2025-05-12 Add everything except pico + headers
2025-05-12 Update gitignore
2025-05-12 add all but pico
2025-05-12 swap to pico
2025-05-13 make pcb
2025-05-13 Finish PCB i think
2025-05-14 modify pcb
2025-05-15 rf tune
2025-05-16 pcb v1
2025-05-17 finishing touches
2025-05-21 finish tracker with dedicated RF
2025-05-22 add direwolf PCB v1
2025-05-22 add BOMs and change readme
2025-05-22 Fix typo
2025-05-22 add version no
2025-05-23 add BOM
2025-05-24 add BOMs
2025-05-24 3d models
2025-05-24 fix crystal
